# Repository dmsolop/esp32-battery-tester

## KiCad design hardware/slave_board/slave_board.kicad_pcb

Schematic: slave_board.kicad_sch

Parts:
F1: 25A; Fuse_2920_7451Metric_Pad2.10x5.45mm_HandSolder
F3: 200mA_60V; Fuse_1206_3216Metric_Pad1.42x1.75mm_HandSolder
J1: RJ45_Shielded; RJ45_Amphenol_RJHSE5380
J2: KLS1-DC-005A-2.5; BarrelJack_Horizontal
J_PWR1: XT60PW-M; AMASS_XT60PW-M_1x02_P7.20mm_Horizontal
J_SENSE1: Micro-Fit 3.0 1x02; Molex_Micro-Fit_3.0_43650-0200_1x02_P3.00mm_Horizontal
J_TEMP1: Micro-Fit 3.0 2x02; Molex_Micro-Fit_3.0_43045-0400_2x02_P3.00mm_Horizontal

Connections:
1W_DATA: J1.8, J_TEMP1.2; also elsewhere on the board
+3.3V: J1.3, J_TEMP1.1; also elsewhere on the board
+12V: J2.1; also elsewhere on the board
ADC_ALERT: J1.7; also elsewhere on the board
FAN_PWM: J1.6; also elsewhere on the board
GND: F3.1, J2.2, J_TEMP1.3; also elsewhere on the board
I2C_SCL: J1.5; also elsewhere on the board
I2C_SDA: J1.4; also elsewhere on the board
LOAD_FORCE_+: F1.1; also elsewhere on the board
LOAD_FORCE_-: J_PWR1.2; also elsewhere on the board
LOAD_SENSE_+: J_SENSE1.1; also elsewhere on the board
LOAD_SENSE_-: J_SENSE1.2; also elsewhere on the board
unnamed: F3.2, J1.2, J1.SH
unnamed: F1.2, J_PWR1.1
PWM_IN: J1.1; also elsewhere on the board

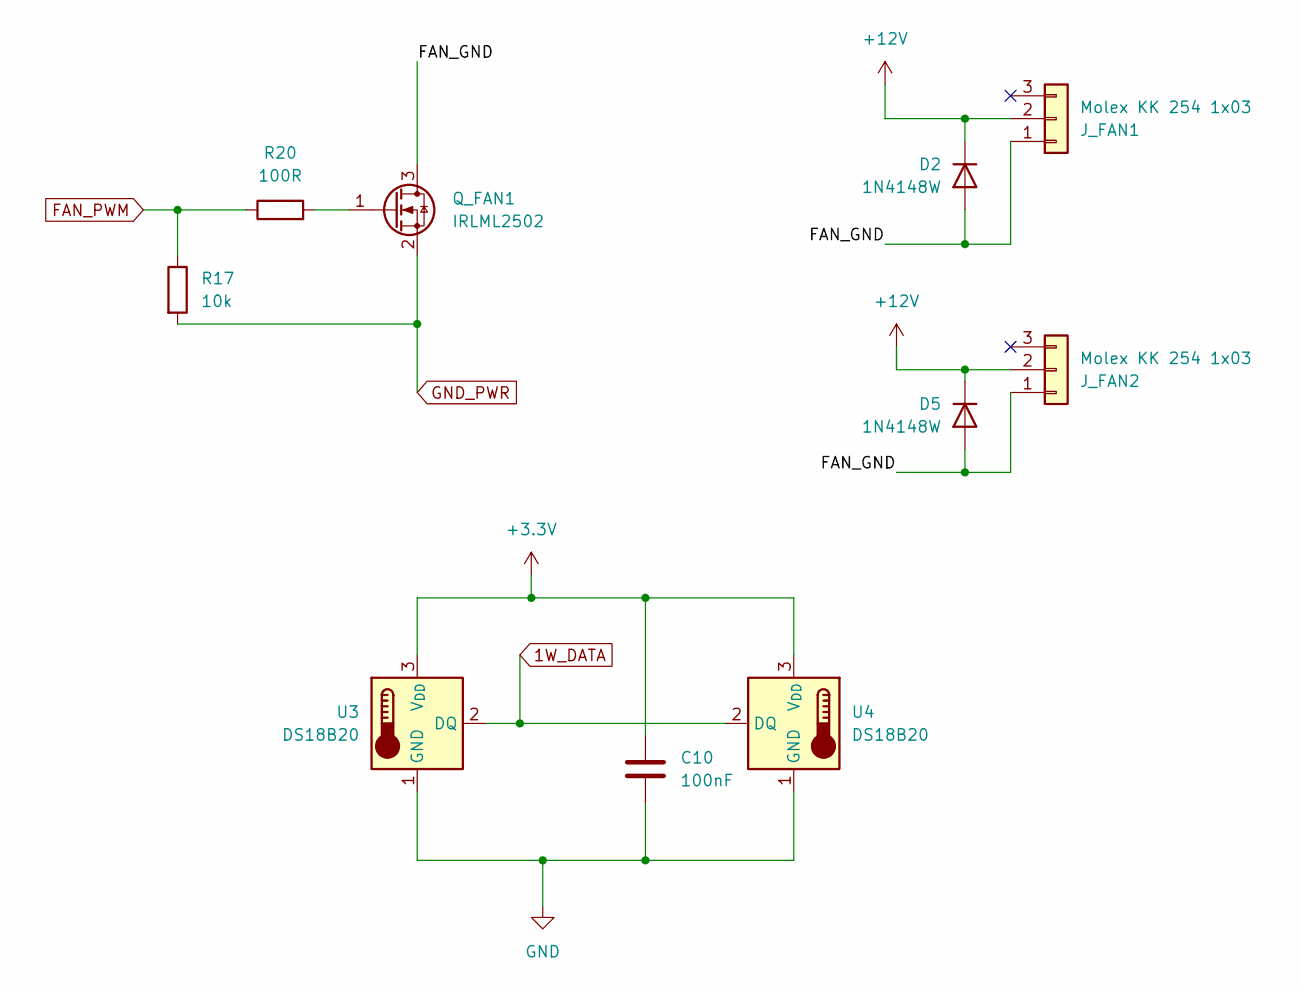
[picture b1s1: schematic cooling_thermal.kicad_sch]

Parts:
C10: 100nF; C_0805_2012Metric_Pad1.18x1.45mm_HandSolder
D2, D5: 1N4148W; Nexperia_CFP3_SOD-123W
J_FAN1, J_FAN2: Molex KK 254 1x03; Molex_KK-254_AE-6410-03A_1x03_P2.54mm_Vertical
Q_FAN1: IRLML2502; SOT-23_Handsoldering
R17: 10k; R_0805_2012Metric_Pad1.20x1.40mm_HandSolder
R20: 100R; R_0805_2012Metric_Pad1.20x1.40mm_HandSolder
U3, U4: DS18B20; TO-92_Inline_W4.0mm_Horizontal_FlatSideUp

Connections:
1W_DATA: U3.2 (DQ), U4.2 (DQ); also elsewhere on the board
+3.3V: C10.1, U3.3 (V_{DD}), U4.3 (V_{DD}); also elsewhere on the board
+12V: D2.1 (K), D5.1 (K), J_FAN1.2, J_FAN2.2; also elsewhere on the board
/cooling_thermal/FAN_GND: D2.2 (A), D5.2 (A), J_FAN1.1, J_FAN2.1, Q_FAN1.3 (D)
FAN_PWM: R17.1, R20.1; also elsewhere on the board
GND: C10.2, U3.1 (GND), U4.1 (GND); also elsewhere on the board
GND_PWR: Q_FAN1.2 (S), R17.2; also elsewhere on the board
unnamed: Q_FAN1.1 (G), R20.2

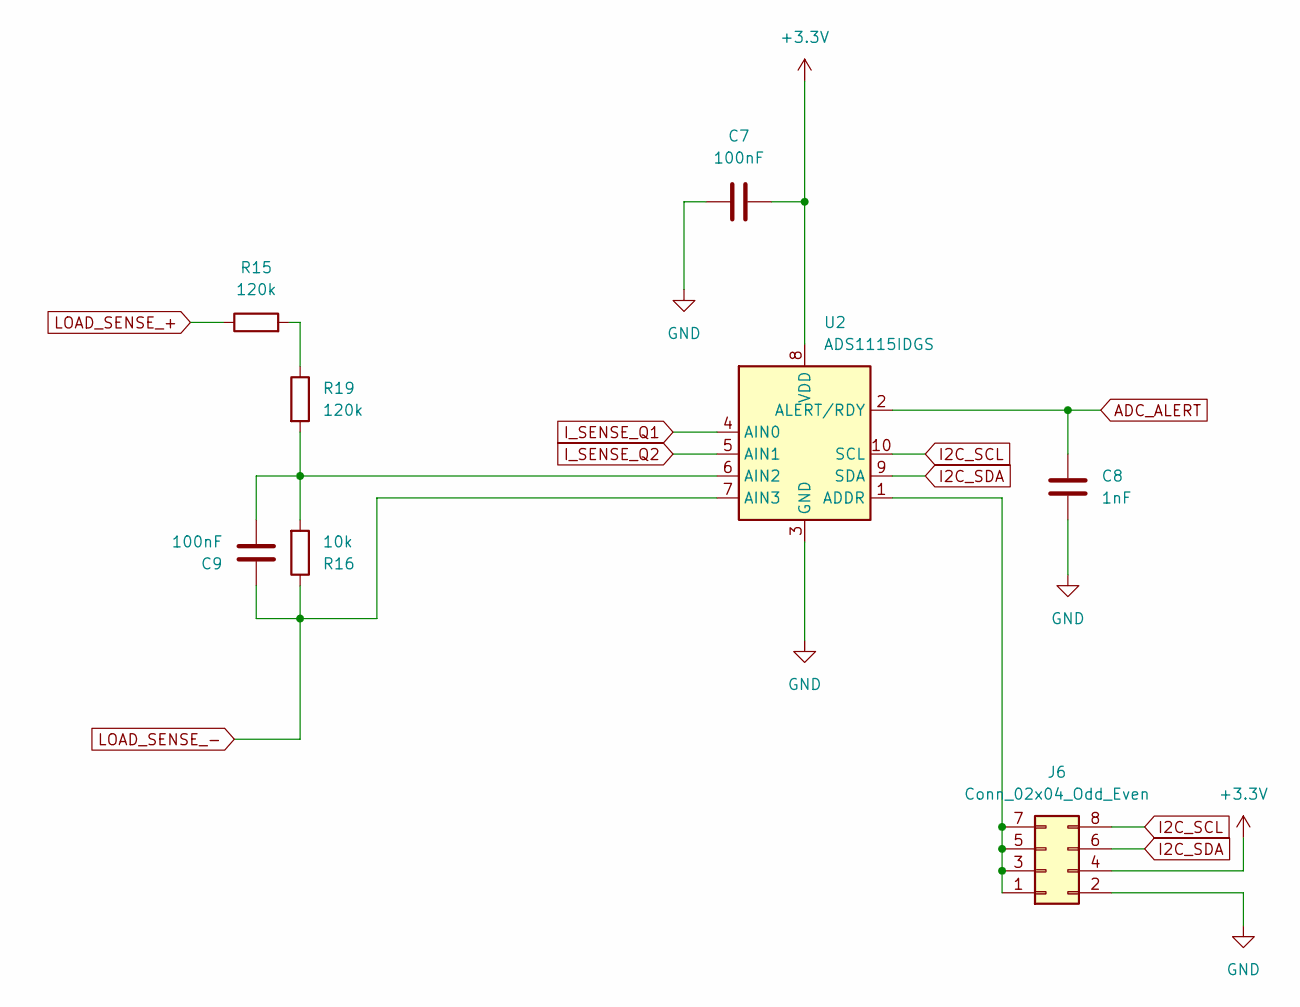
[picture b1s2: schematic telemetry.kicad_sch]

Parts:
C7, C9: 100nF; C_0805_2012Metric_Pad1.18x1.45mm_HandSolder
C8: 1nF; C_0805_2012Metric_Pad1.18x1.45mm_HandSolder
J6: Conn_02x04_Odd_Even; PinHeader_2x04_P2.54mm_Vertical
R15, R19: 120k; R_1206_3216Metric_Pad1.30x1.75mm_HandSolder
R16: 10k; R_0805_2012Metric_Pad1.20x1.40mm_HandSolder
U2: ADS1115IDGS; TSSOP-10_3x3mm_P0.5mm

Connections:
+3.3V: C7.2, J6.4, U2.8 (VDD); also elsewhere on the board
ADC_ALERT: C8.1, U2.2 (ALERT/RDY); also elsewhere on the board
GND: C7.1, C8.2, J6.2, U2.3 (GND); also elsewhere on the board
I2C_SCL: J6.8, U2.10 (SCL); also elsewhere on the board
I2C_SDA: J6.6, U2.9 (SDA); also elsewhere on the board
I_SENSE_Q1: U2.4 (AIN0); also elsewhere on the board
I_SENSE_Q2: U2.5 (AIN1); also elsewhere on the board
LOAD_SENSE_+: R15.1; also elsewhere on the board
LOAD_SENSE_-: C9.1, R16.1, U2.7 (AIN3); also elsewhere on the board
unnamed: J6.1, J6.3, J6.5, J6.7, U2.1 (ADDR)
unnamed: R15.2, R19.1
unnamed: C9.2, R16.2, R19.2, U2.6 (AIN2)

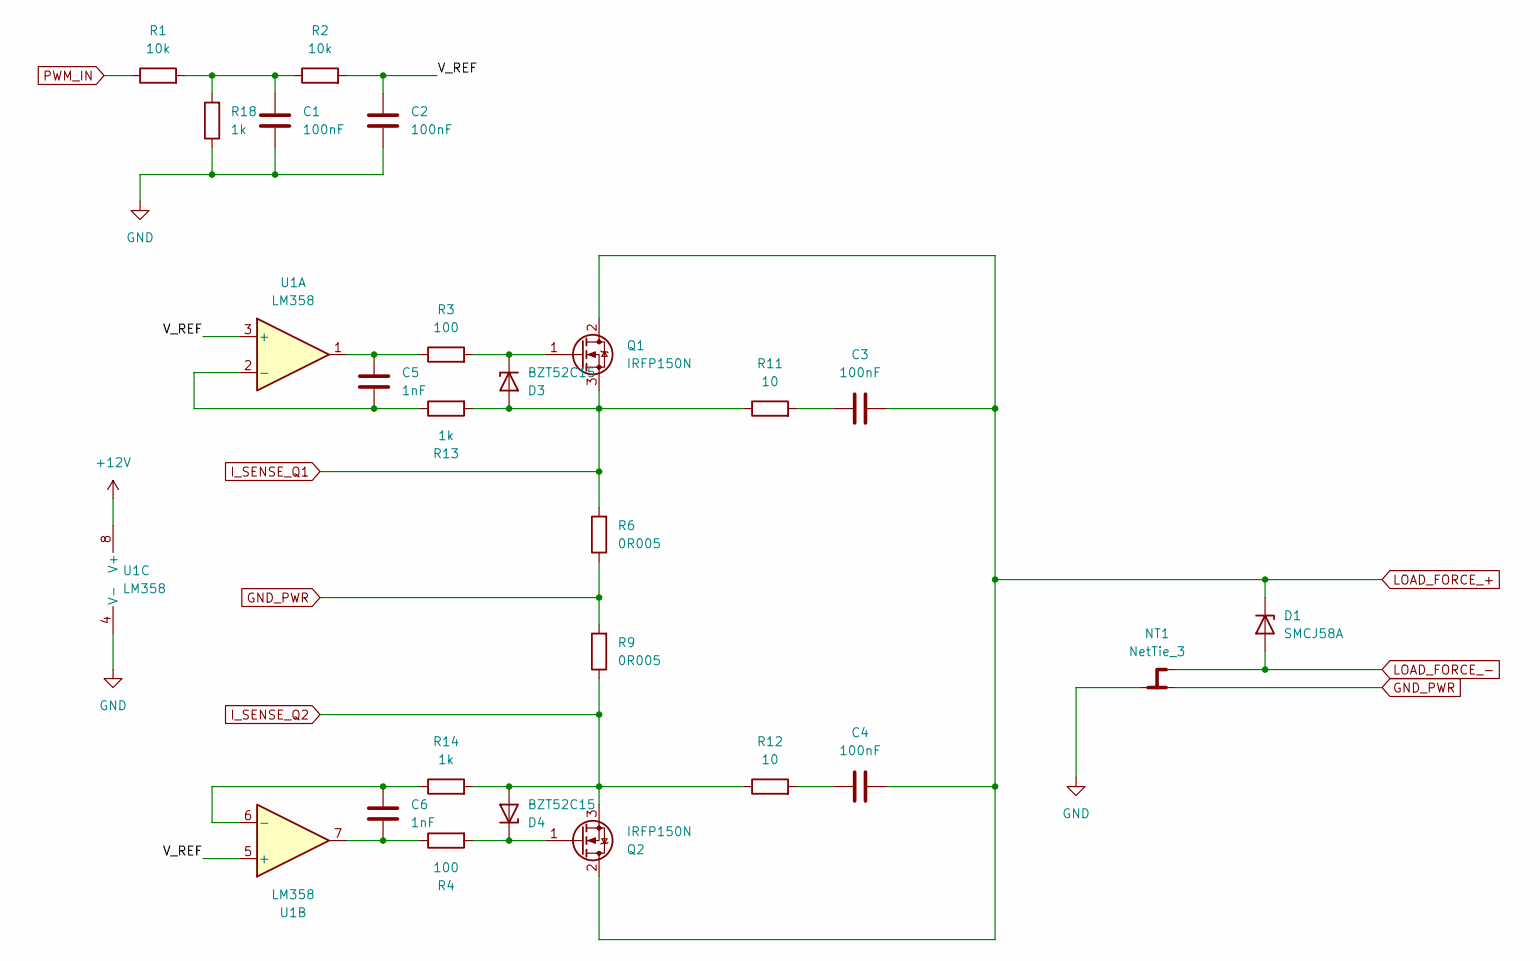
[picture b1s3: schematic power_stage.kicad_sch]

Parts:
C1, C2: 100nF; C_0805_2012Metric_Pad1.18x1.45mm_HandSolder
C3, C4: 100nF; C_1206_3216Metric_Pad1.33x1.80mm_HandSolder
C5, C6: 1nF; C_0805_2012Metric_Pad1.18x1.45mm_HandSolder
D1: SMCJ58A; D_SMC-RM10_Universal_Handsoldering
D3, D4: BZT52C15; D_SOD-123
NT1: NetTie_3; NetTie-3_SMD_Pad2.0mm
Q1, Q2: IRFP150N; TO-247-3_Horizontal_TabUp
R1, R2: 10k; R_0805_2012Metric_Pad1.20x1.40mm_HandSolder
R3, R4: 100; R_0805_2012Metric_Pad1.20x1.40mm_HandSolder
R6, R9: 0R005; R_2512_6332Metric_Pad1.40x3.35mm_HandSolder
R11, R12: 10; R_1206_3216Metric_Pad1.30x1.75mm_HandSolder
R13, R14, R18: 1k; R_0805_2012Metric_Pad1.20x1.40mm_HandSolder
U1: LM358; SOIC-8_3.9x4.9mm_P1.27mm

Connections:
+12V: U1.8 (V+); also elsewhere on the board
/Power_Stage/V_REF: C2.1, R2.2, U1.3 (+), U1.5 (+)
GND: C1.2, C2.2, NT1.2, R18.1, U1.4 (V-); also elsewhere on the board
GND_PWR: NT1.1, R6.1, R9.2; also elsewhere on the board
I_SENSE_Q1: D3.2 (A), Q1.3 (S), R6.2, R11.1, R13.2; also elsewhere on the board
I_SENSE_Q2: D4.2 (A), Q2.3 (S), R9.1, R12.1, R14.2; also elsewhere on the board
LOAD_FORCE_+: C3.2, C4.2, D1.1 (K), Q1.2 (D), Q2.2 (D); also elsewhere on the board
LOAD_FORCE_-: D1.2 (A), NT1.3; also elsewhere on the board
unnamed: C1.1, R1.2, R2.1, R18.2
unnamed: C3.1, R11.2
unnamed: C4.1, R12.2
unnamed: C5.1, R3.1, U1.1
unnamed: C6.2, R4.1, U1.7
unnamed: D3.1 (K), Q1.1 (G), R3.2
unnamed: D4.1 (K), Q2.1 (G), R4.2
unnamed: C5.2, R13.1, U1.2 (-)
unnamed: C6.1, R14.1, U1.6 (-)
PWM_IN: R1.1; also elsewhere on the board

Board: 2 copper layers, 49 parts (0 on the bottom side), 33 nets, no tracks yet.

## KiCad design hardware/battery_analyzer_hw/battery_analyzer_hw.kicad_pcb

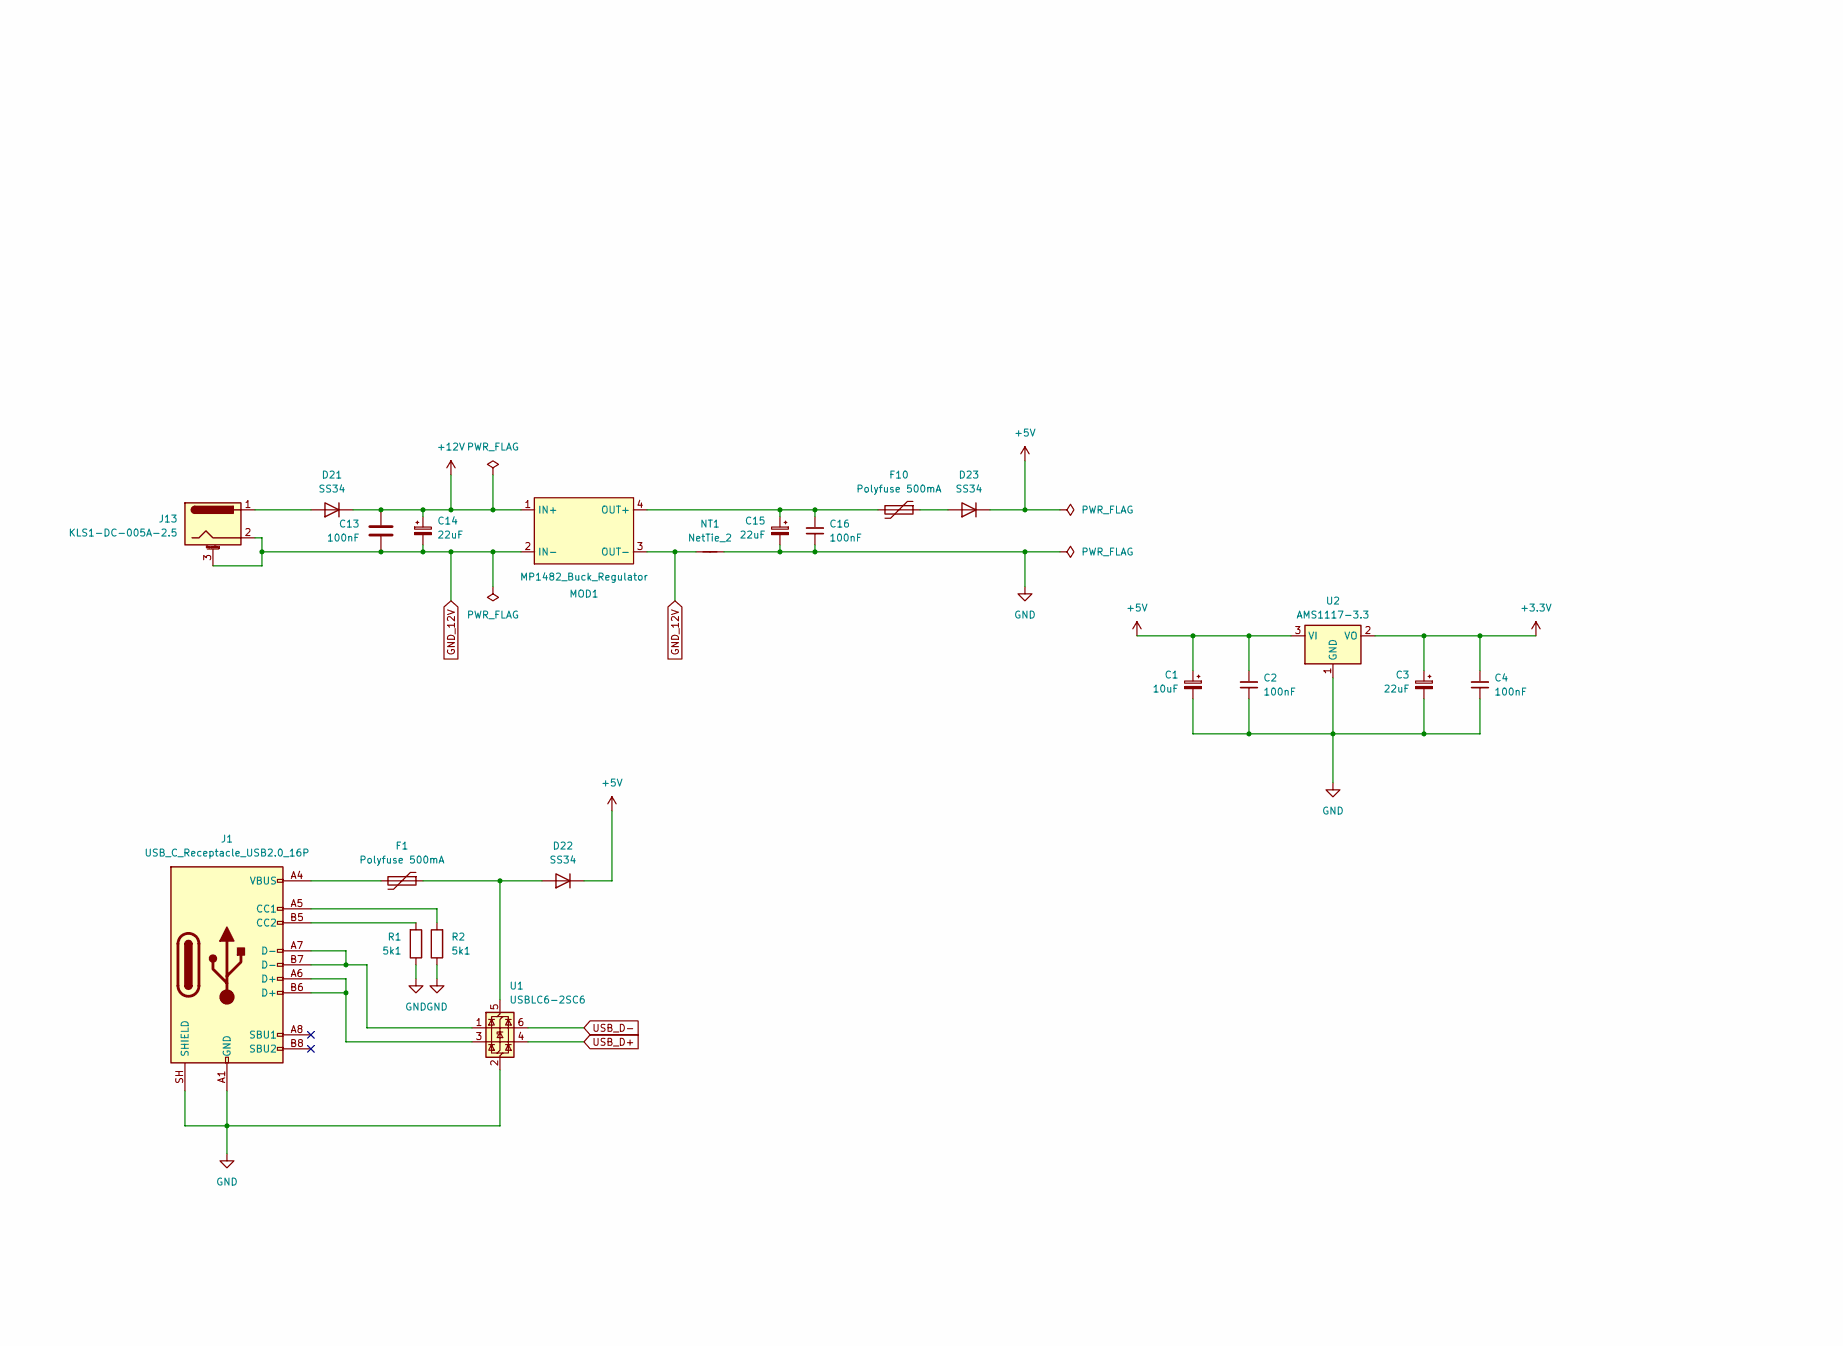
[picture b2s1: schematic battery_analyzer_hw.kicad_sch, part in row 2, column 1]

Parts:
C1: 10uF; CP_EIA-3216-18_Kemet-A_HandSolder
C2, C4, C13, C16: 100nF; C_0805_2012Metric_Pad1.18x1.45mm_HandSolder
C3, C15: 22uF; CP_EIA-3528-21_Kemet-B_HandSolder
C14: 22uF; CP_EIA-7343-31_Kemet-D_HandSolder
D21, D22, D23: SS34; D_SMA_Handsoldering
F1, F10: Polyfuse 500mA; Fuse_1206_3216Metric_Pad1.42x1.75mm_HandSolder
J1: USB_C_Receptacle_USB2.0_16P; USB_C_Receptacle_GCT_USB4105-xx-A_16P_TopMnt_Horizontal
J13: KLS1-DC-005A-2.5; BarrelJack_Horizontal
MOD1: MP1482_Buck_Regulator; DC_DC_MP1482_18x12mm_SMD
NT1: NetTie_2; NetTie-2_SMD_Pad0.5mm
R1, R2: 5k1; R_0805_2012Metric_Pad1.20x1.40mm_HandSolder
U1: USBLC6-2SC6; SOT-23-6_Handsoldering
U2: AMS1117-3.3; SOT-223-3_TabPin2

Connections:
+3.3V: C3.1, C4.1, U2.2 (VO); also elsewhere on the board
+5V: C1.1, C2.1, D22.1 (K), D23.1 (K), U2.3 (VI)
+12V: C13.1, C14.1, D21.1 (K), MOD1.1 (IN+); also elsewhere on the board
GND: C1.2, C2.2, C3.2, C4.2, C15.2, C16.2, J1.A1 (GND), J1.A12 (GND), J1.B1 (GND), J1.B12 (GND), J1.SH (SHIELD), NT1.2, R1.1, R2.1, U1.2 (GND), U2.1 (GND); also elsewhere on the board
GND_12V: C13.2, C14.2, J13.2, J13.3 (MountPin_3), MOD1.2 (IN-), MOD1.3 (OUT-), NT1.1; also elsewhere on the board
unnamed: D21.2 (A), J13.1
unnamed: D22.2 (A), F1.1, U1.5 (VBUS)
unnamed: D23.2 (A), F10.1
unnamed: F1.2, J1.A4 (VBUS), J1.A9 (VBUS), J1.B4 (VBUS), J1.B9 (VBUS)
unnamed: J1.A5 (CC1), R2.2
unnamed: J1.B5 (CC2), R1.2
unnamed: J1.A6 (D+), J1.B6 (D+), U1.3 (I/O2)
unnamed: J1.A7 (D-), J1.B7 (D-), U1.1 (I/O1)
unnamed: C15.1, C16.1, F10.2, MOD1.4 (OUT+)
USB_D+: U1.4 (I/O2); also elsewhere on the board
USB_D-: U1.6 (I/O1); also elsewhere on the board

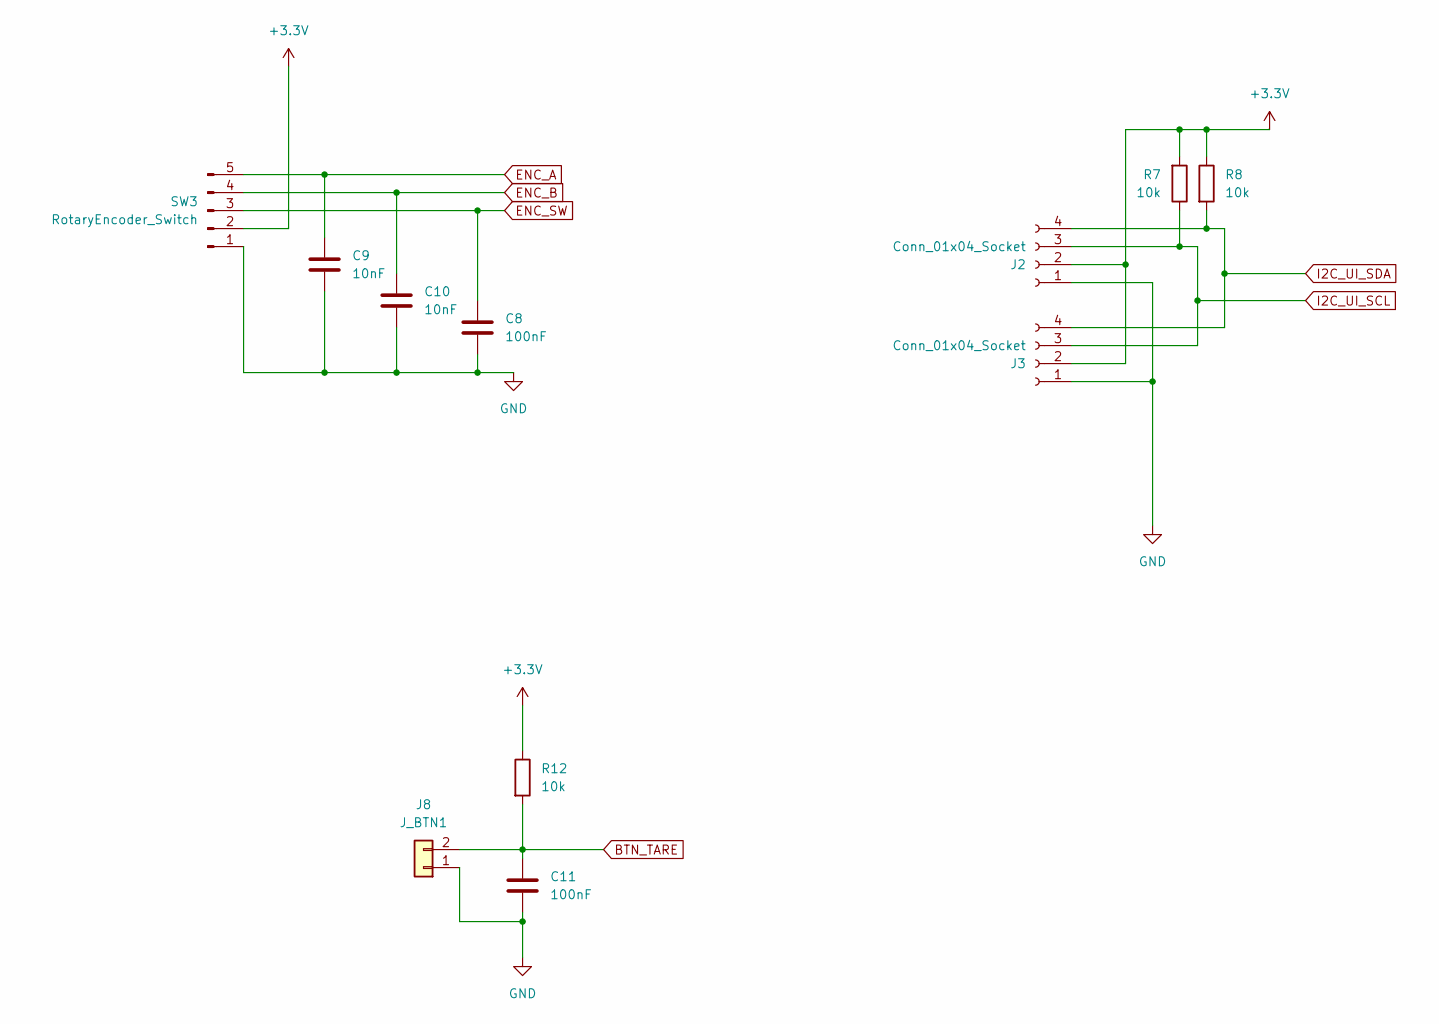
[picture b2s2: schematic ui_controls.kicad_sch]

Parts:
C8, C11: 100nF; C_0805_2012Metric_Pad1.18x1.45mm_HandSolder
C9, C10: 10nF; C_0805_2012Metric_Pad1.18x1.45mm_HandSolder
J2, J3: Conn_01x04_Socket; PinHeader_1x04_P2.54mm_Vertical
J8: J_BTN1; PinHeader_1x02_P2.54mm_Vertical
R7, R8, R12: 10k; R_0805_2012Metric_Pad1.20x1.40mm_HandSolder
SW3: RotaryEncoder_Switch; PinHeader_1x05_P2.54mm_Vertical

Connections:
+3.3V: J2.2, J3.2, R7.2, R8.1, R12.1, SW3.2; also elsewhere on the board
BTN_TARE: C11.1, J8.2, R12.2; also elsewhere on the board
ENC_A: C9.1, SW3.5; also elsewhere on the board
ENC_B: C10.1, SW3.4; also elsewhere on the board
ENC_SW: C8.1, SW3.3; also elsewhere on the board
GND: C8.2, C9.2, C10.2, C11.2, J2.1, J3.1, J8.1, SW3.1; also elsewhere on the board
I2C_UI_SCL: J2.3, J3.3, R7.1; also elsewhere on the board
I2C_UI_SDA: J2.4, J3.4, R8.2; also elsewhere on the board

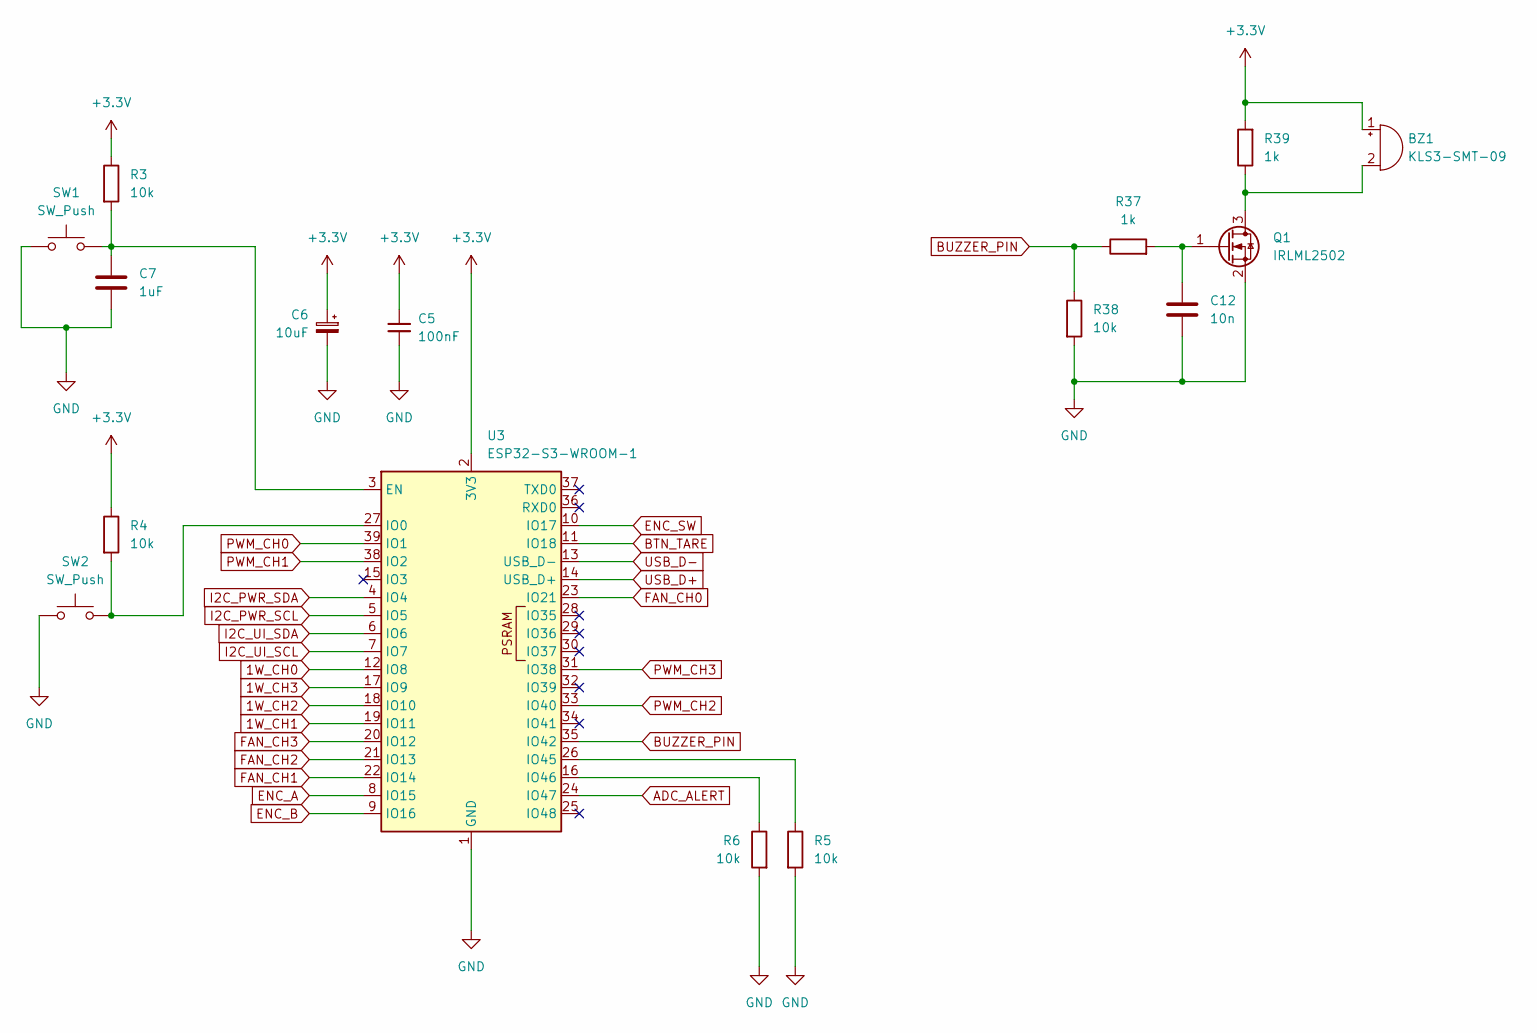
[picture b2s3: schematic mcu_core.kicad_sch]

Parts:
BZ1: KLS3-SMT-09; Buzzer_Murata_PKMCS0909E
C5: 100nF; C_0805_2012Metric_Pad1.18x1.45mm_HandSolder
C6: 10uF; CP_EIA-3216-18_Kemet-A_HandSolder
C7: 1uF; C_0805_2012Metric_Pad1.18x1.45mm_HandSolder
C12: 10n; C_0805_2012Metric_Pad1.18x1.45mm_HandSolder
Q1: IRLML2502; SOT-23_Handsoldering
R3, R4, R5, R6, R38: 10k; R_0805_2012Metric_Pad1.20x1.40mm_HandSolder
R37, R39: 1k; R_0805_2012Metric_Pad1.20x1.40mm_HandSolder
SW1, SW2: SW_Push; SW_PUSH_6mm
U3: ESP32-S3-WROOM-1

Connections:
1W_CH0: U3.12 (IO8); also elsewhere on the board
1W_CH1: U3.19 (IO11); also elsewhere on the board
1W_CH2: U3.18 (IO10); also elsewhere on the board
1W_CH3: U3.17 (IO9); also elsewhere on the board
+3.3V: BZ1.1 (+), C5.1, C6.1, R3.1, R4.1, R39.2, U3.2 (3V3); also elsewhere on the board
ADC_ALERT: U3.24 (IO47); also elsewhere on the board
BTN_TARE: U3.11 (IO18); also elsewhere on the board
BUZZER_PIN: R37.1, R38.1, U3.35 (IO42)
ENC_A: U3.8 (IO15); also elsewhere on the board
ENC_B: U3.9 (IO16); also elsewhere on the board
ENC_SW: U3.10 (IO17); also elsewhere on the board
FAN_CH0: U3.23 (IO21); also elsewhere on the board
FAN_CH1: U3.22 (IO14); also elsewhere on the board
FAN_CH2: U3.21 (IO13); also elsewhere on the board
FAN_CH3: U3.20 (IO12); also elsewhere on the board
GND: C5.2, C6.2, C7.2, C12.2, Q1.2 (S), R5.2, R6.2, R38.2, SW1.1, SW2.1, U3.1 (GND), U3.40 (GND), U3.41 (GND); also elsewhere on the board
I2C_PWR_SCL: U3.5 (IO5); also elsewhere on the board
I2C_PWR_SDA: U3.4 (IO4); also elsewhere on the board
I2C_UI_SCL: U3.7 (IO7); also elsewhere on the board
I2C_UI_SDA: U3.6 (IO6); also elsewhere on the board
unnamed: BZ1.2 (-), Q1.3 (D), R39.1
unnamed: C12.1, Q1.1 (G), R37.2
unnamed: C7.1, R3.2, SW1.2, U3.3 (EN)
unnamed: R4.2, SW2.2, U3.27 (IO0)
unnamed: R5.1, U3.26 (IO45)
unnamed: R6.1, U3.16 (IO46)
PWM_CH0: U3.39 (IO1); also elsewhere on the board
PWM_CH1: U3.38 (IO2); also elsewhere on the board
PWM_CH2: U3.33 (IO40); also elsewhere on the board
PWM_CH3: U3.31 (IO38); also elsewhere on the board
USB_D+: U3.14 (USB_D+); also elsewhere on the board
USB_D-: U3.13 (USB_D-); also elsewhere on the board

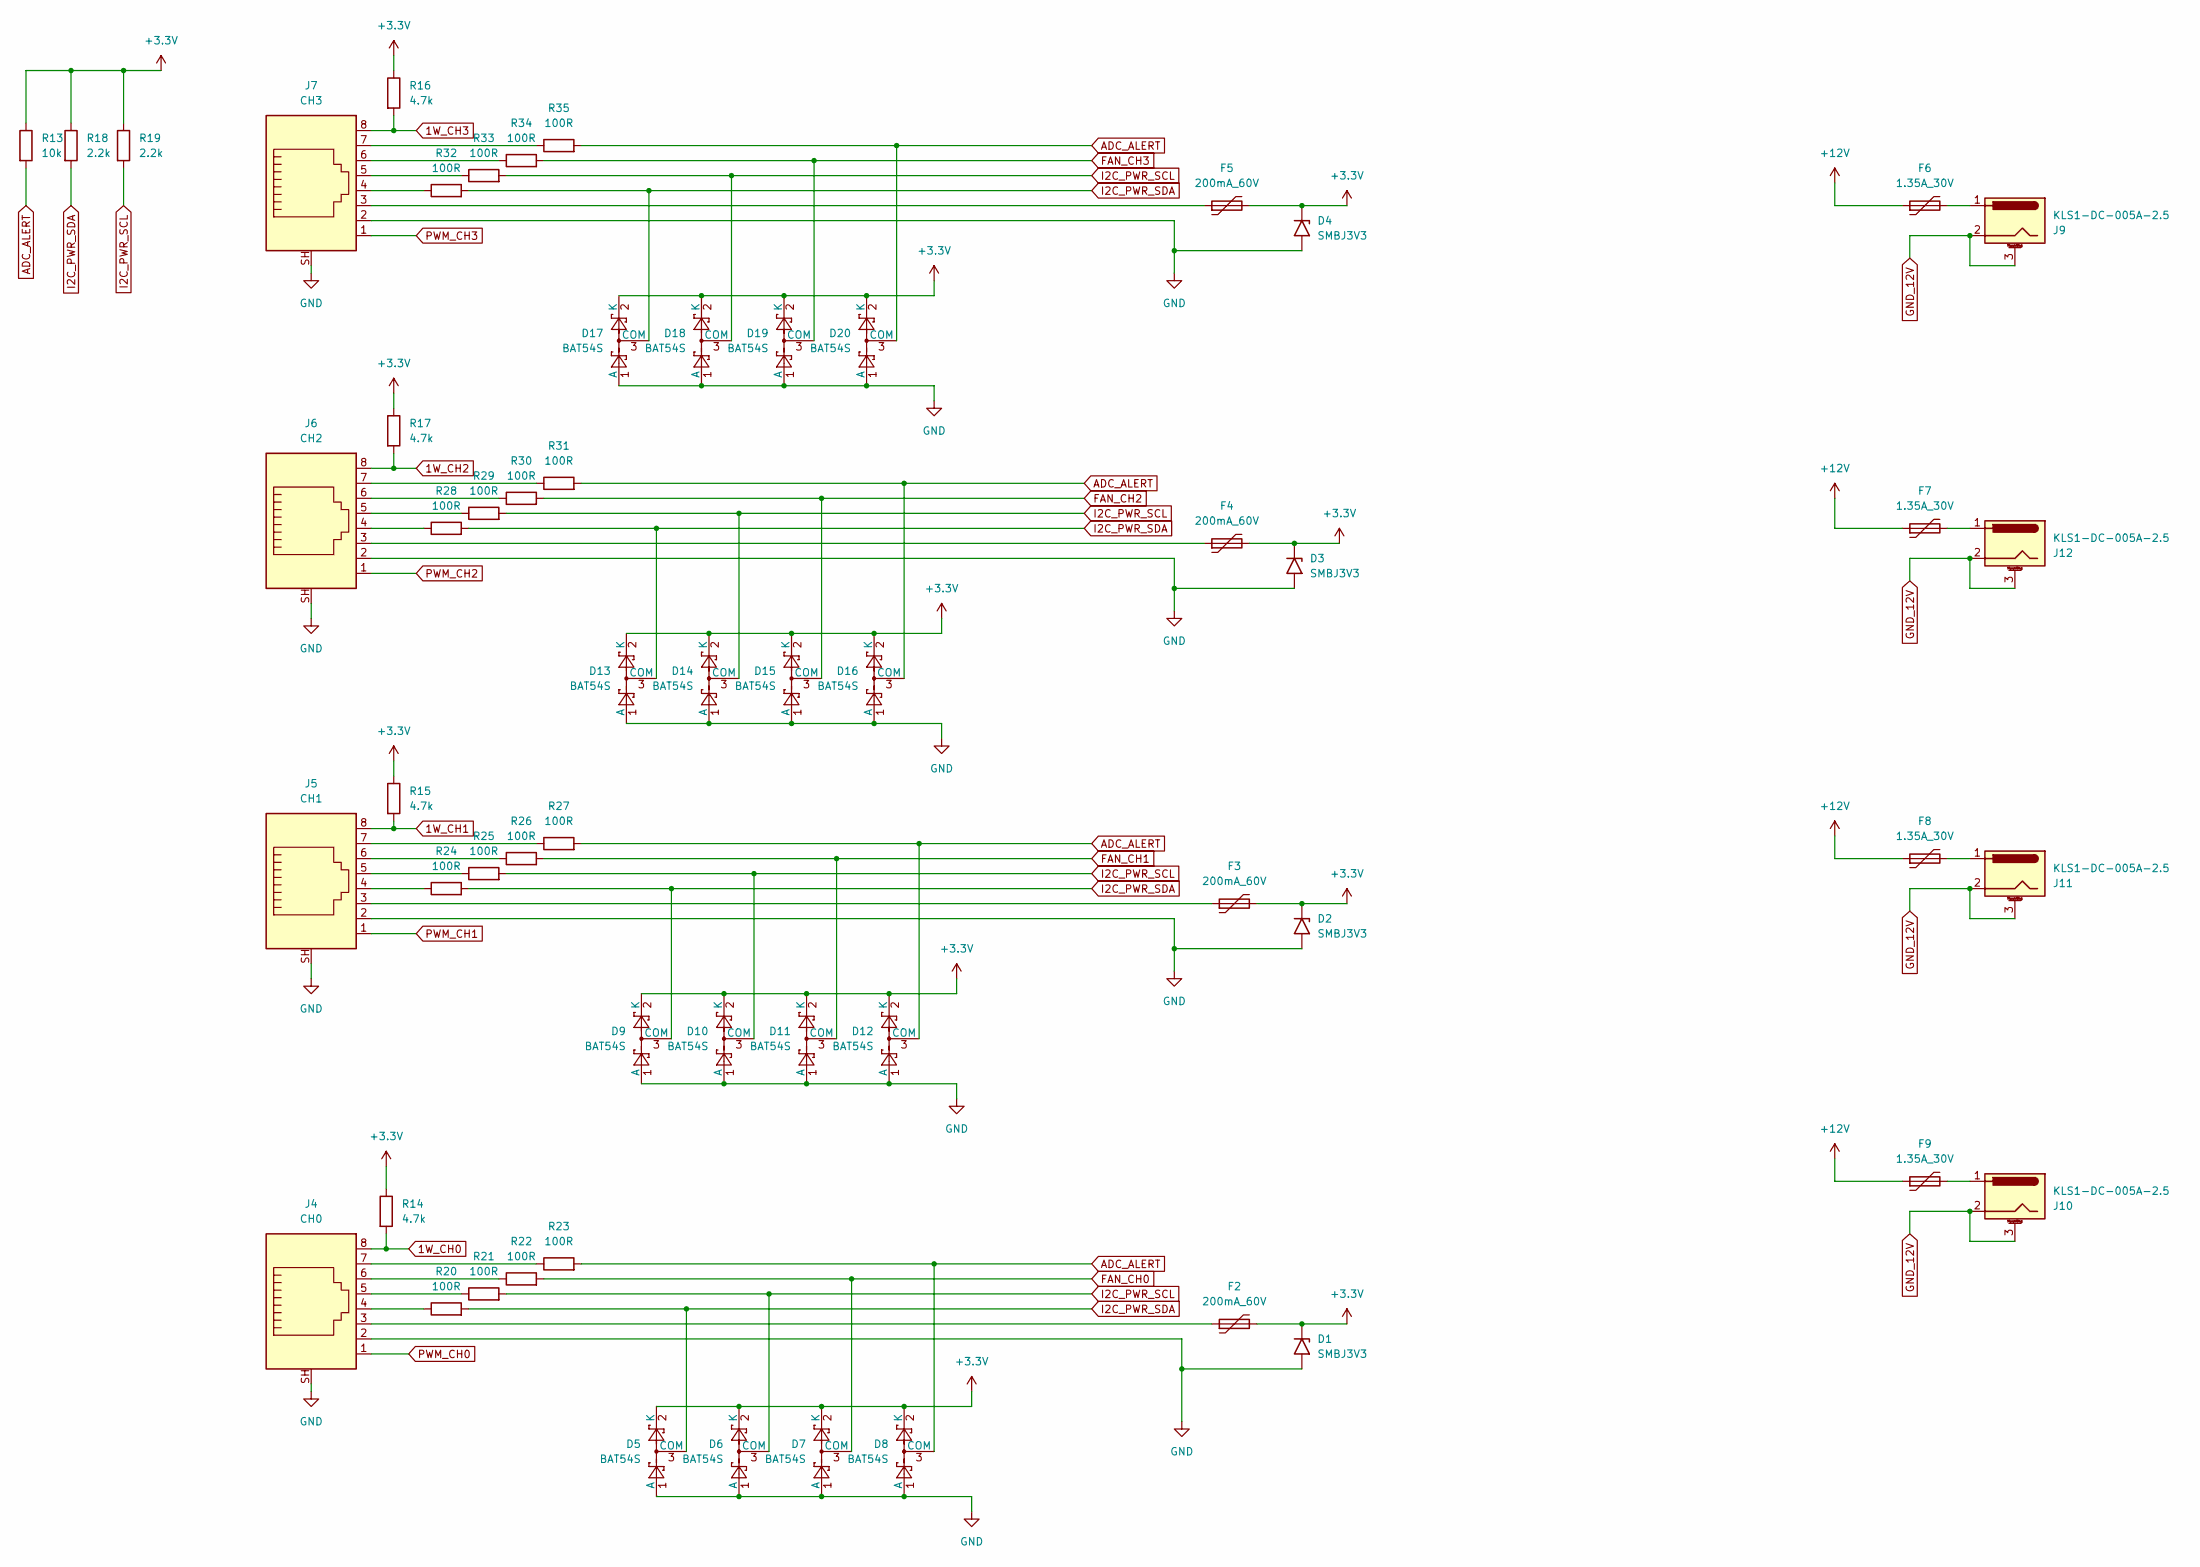
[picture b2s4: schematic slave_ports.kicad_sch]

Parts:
D1, D2, D3, D4: SMBJ3V3; D_SMB_Handsoldering
D5, D6, D7, D8, D9, D10, D11, D12, D13, D14, D15, D16, D17, D18, D19, D20: BAT54S; SOT-23_Handsoldering
F2, F3, F4, F5: 200mA_60V; Fuse_1206_3216Metric_Pad1.42x1.75mm_HandSolder
F6, F7, F8, F9: 1.35A_30V; Fuse_Bourns_MF-RHT100
J4: CH0; RJ45_Amphenol_RJHSE5380
J5: CH1; RJ45_Amphenol_RJHSE5380
J6: CH2; RJ45_Amphenol_RJHSE5380
J7: CH3; RJ45_Amphenol_RJHSE5380
J9, J10, J11, J12: KLS1-DC-005A-2.5; BarrelJack_Horizontal
R13: 10k; R_0805_2012Metric_Pad1.20x1.40mm_HandSolder
R14, R15, R16, R17: 4.7k; R_0805_2012Metric_Pad1.20x1.40mm_HandSolder
R18, R19: 2.2k; R_0805_2012Metric_Pad1.20x1.40mm_HandSolder
R20, R21, R22, R23, R24, R25, R26, R27, R28, R29, R30, R31, R32, R33, R34, R35: 100R; R_0805_2012Metric_Pad1.20x1.40mm_HandSolder

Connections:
1W_CH0: J4.8, R14.2; also elsewhere on the board
1W_CH1: J5.8, R15.2; also elsewhere on the board
1W_CH2: J6.8, R17.2; also elsewhere on the board
1W_CH3: J7.8, R16.2; also elsewhere on the board
+3.3V: D1.1 (A1), D2.1 (A1), D3.1 (A1), D4.1 (A1), D5.2 (K), D6.2 (K), D7.2 (K), D8.2 (K), D9.2 (K), D10.2 (K), D11.2 (K), D12.2 (K), D13.2 (K), D14.2 (K), D15.2 (K), D16.2 (K), D17.2 (K), D18.2 (K), D19.2 (K), D20.2 (K), F2.2, F3.2, F4.2, F5.2, R13.1, R14.1, R15.1, R16.1, R17.1, R18.1, R19.1; also elsewhere on the board
+12V: F6.1, F7.1, F8.1, F9.1; also elsewhere on the board
ADC_ALERT: D8.3 (COM), D12.3 (COM), D16.3 (COM), D20.3 (COM), R13.2, R23.2, R27.2, R31.2, R35.2; also elsewhere on the board
FAN_CH0: D7.3 (COM), R22.2; also elsewhere on the board
FAN_CH1: D11.3 (COM), R26.2; also elsewhere on the board
FAN_CH2: D15.3 (COM), R30.2; also elsewhere on the board
FAN_CH3: D19.3 (COM), R34.2; also elsewhere on the board
GND: D1.2 (A2), D2.2 (A2), D3.2 (A2), D4.2 (A2), D5.1 (A), D6.1 (A), D7.1 (A), D8.1 (A), D9.1 (A), D10.1 (A), D11.1 (A), D12.1 (A), D13.1 (A), D14.1 (A), D15.1 (A), D16.1 (A), D17.1 (A), D18.1 (A), D19.1 (A), D20.1 (A), J4.2, J4.SH, J5.2, J5.SH, J6.2, J6.SH, J7.2, J7.SH; also elsewhere on the board
GND_12V: J9.2, J9.3 (MountPin_3), J10.2, J10.3 (MountPin_3), J11.2, J11.3 (MountPin_3), J12.2, J12.3 (MountPin_3); also elsewhere on the board
I2C_PWR_SCL: D6.3 (COM), D10.3 (COM), D14.3 (COM), D18.3 (COM), R19.2, R21.2, R25.2, R29.2, R33.2; also elsewhere on the board
I2C_PWR_SDA: D5.3 (COM), D9.3 (COM), D13.3 (COM), D17.3 (COM), R18.2, R20.2, R24.2, R28.2, R32.2; also elsewhere on the board
unnamed: F2.1, J4.3
unnamed: F3.1, J5.3
unnamed: F4.1, J6.3
unnamed: F5.1, J7.3
unnamed: F6.2, J9.1
unnamed: F7.2, J12.1
unnamed: F8.2, J11.1
unnamed: F9.2, J10.1
unnamed: J4.4, R20.1
unnamed: J4.5, R21.1
unnamed: J4.6, R22.1
unnamed: J4.7, R23.1
unnamed: J5.4, R24.1
unnamed: J5.5, R25.1
unnamed: J5.6, R26.1
unnamed: J5.7, R27.1
unnamed: J6.4, R28.1
unnamed: J6.5, R29.1
unnamed: J6.6, R30.1
unnamed: J6.7, R31.1
unnamed: J7.4, R32.1
unnamed: J7.5, R33.1
unnamed: J7.6, R34.1
unnamed: J7.7, R35.1
PWM_CH0: J4.1; also elsewhere on the board
PWM_CH1: J5.1; also elsewhere on the board
PWM_CH2: J6.1; also elsewhere on the board
PWM_CH3: J7.1; also elsewhere on the board

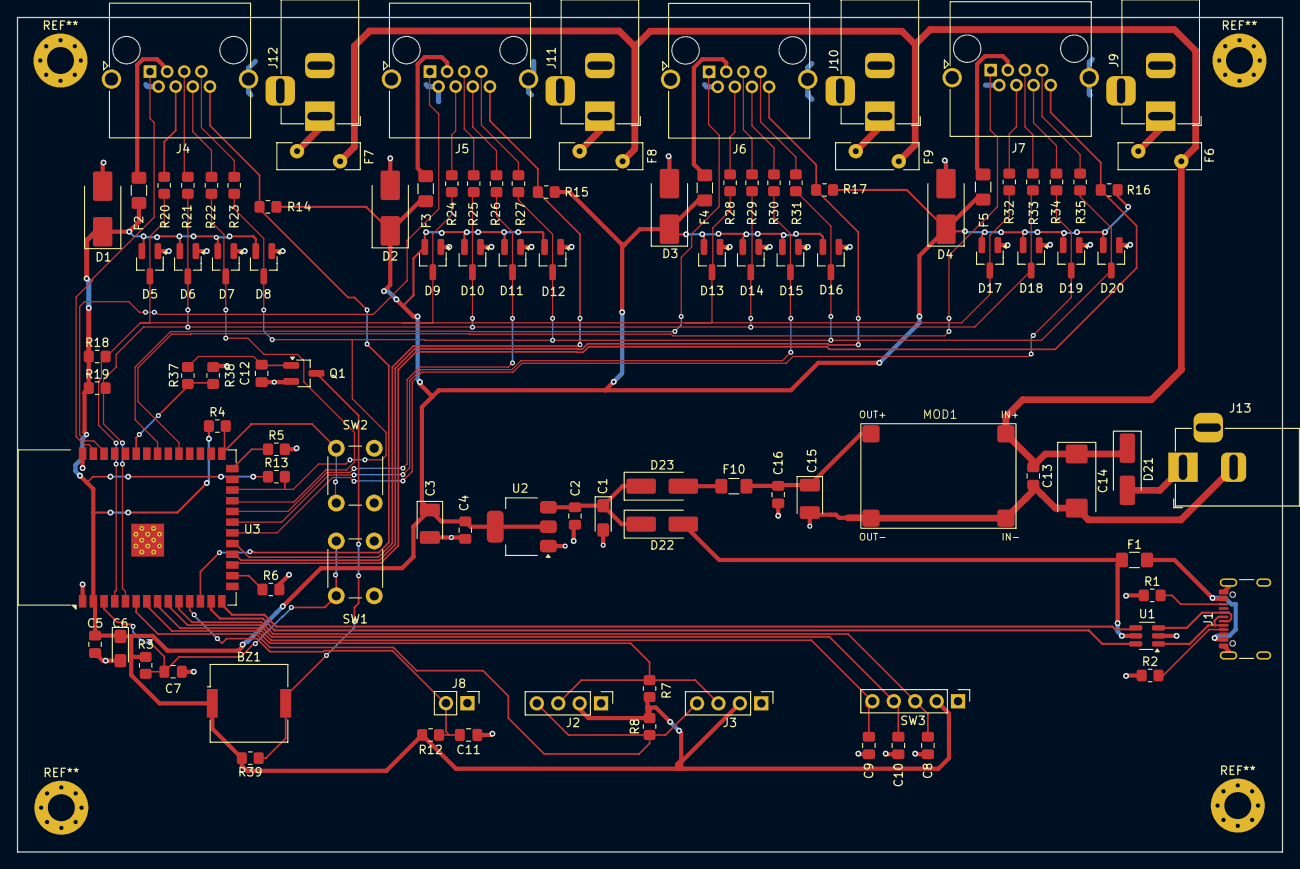
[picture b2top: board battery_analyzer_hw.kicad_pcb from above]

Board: 2 copper layers, 150.0 x 99.0 mm, 107 parts (0 on the bottom side), 68 nets.
